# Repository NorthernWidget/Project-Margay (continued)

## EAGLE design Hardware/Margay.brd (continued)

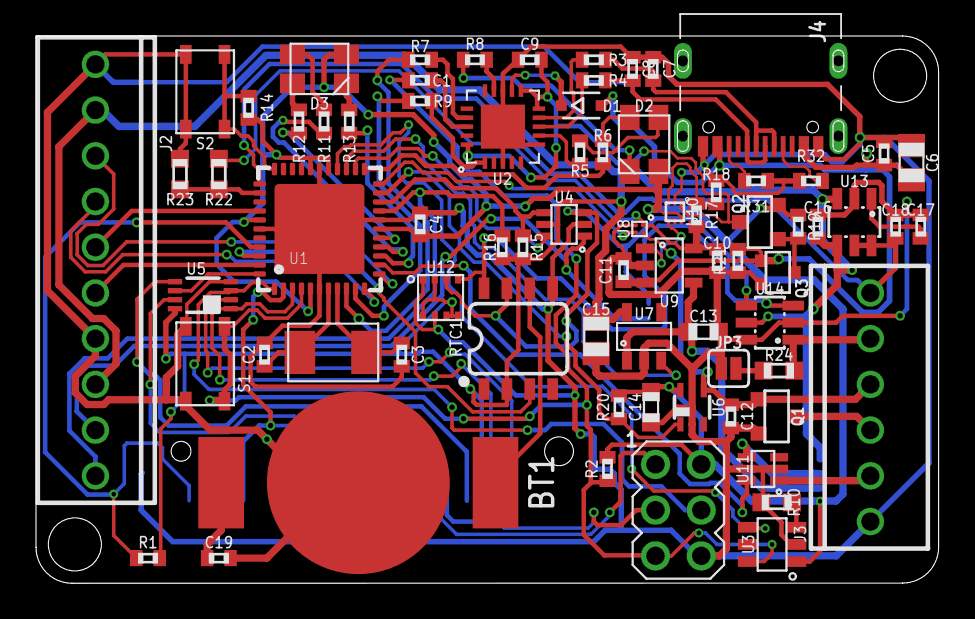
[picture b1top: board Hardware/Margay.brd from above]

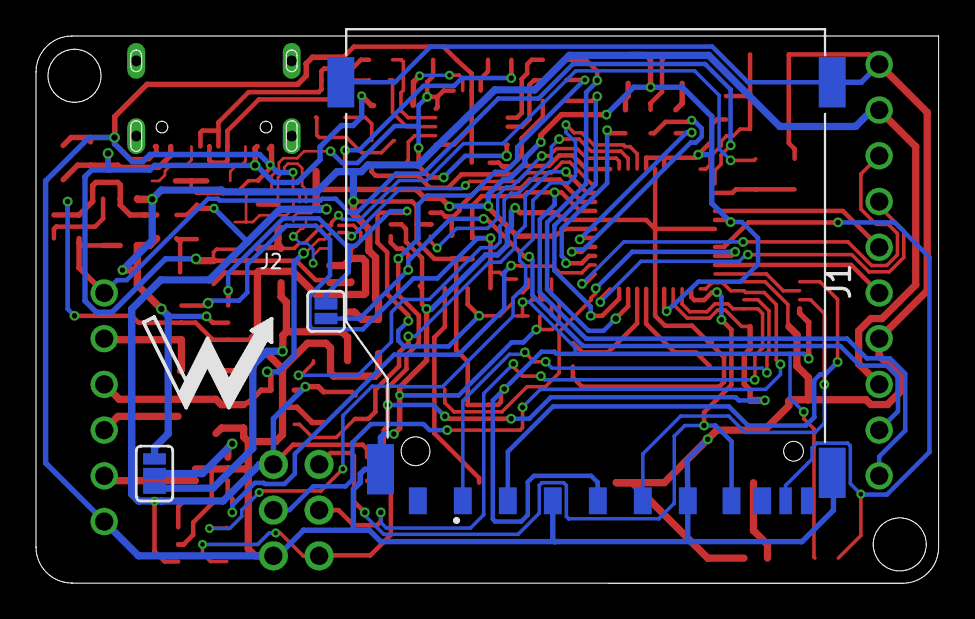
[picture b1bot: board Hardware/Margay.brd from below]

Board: 2 copper layers, 50.1 x 30.4 mm, 82 parts (4 on the bottom side), 72 nets.

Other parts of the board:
U$2: NWLOGO_MED

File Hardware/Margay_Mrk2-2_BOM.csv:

"Qty","Value","Device","Package","Parts","Description","DIGIKEY","DISP","MF","MOUSER","MPN","PROD_ID","VALUE","VALUE_PART",
"1","","CONN_102.54_SCREW","1X10_SCREW","J2","Genaric 10 terminal header","ED10567-ND","","On Shore","","OSTVN10A150","","","",
"11","0.1uF","C-EU0.1UFC0402","C0402","C1, C4, C5, C9, C10, C11, C12, C16, C17, C18, C19","CAPACITOR, European symbol","490-4759-1-ND","","Murata","","GCM155R71C104KA55D","","","",
"2","100k","R-EU_100KR0402","R0402","R10, R19","RESISTOR, European symbol","311-100KLRCT-ND","","Yageo","","RC0402FR-07100KL","","","100k",
"9","10k","R-EU_10KR0402","R0402","R1, R2, R14, R15, R16, R17, R18, R20, R21","RESISTOR, European symbol","311-10.0KLRCT-ND","","Yageo","","RC0402FR-0710KL","","","10k",
"2","10k","R-EU_10KR0603","R0603","R22, R23","RESISTOR, European symbol","311-10.0KHRCT-ND","","Yageo","","RC0603FR-0710KL","","","10k",
"1","10k","R-EU_P10KR0603","R0603","R24","RESISTOR, European symbol","P10KDBCT-ND","","Panasonic","","ERA-3AEB103V","","","10k",
"2","10uF","C-EU10UFC0805","C0805","C6, C15","CAPACITOR, European symbol","490-6473-6-ND","","Murata","","GRM21BR61C106KE15K","","","",
"4","12pF","C-EU12PFC0402","C0402","C2, C3, C7, C8","CAPACITOR, European symbol","445-5585-1-ND","","TDK","","CGA2B2C0G1H120J050BA","","","",
"2","1k","R-EU_1KR0402","R0402","R7, R9","RESISTOR, European symbol","311-1.00KLRCT-ND","","Yageo","","RC0603FR-07330RL","","","1k",
"2","1uF","C-EU1UFC0603","C0603","C13, C14","CAPACITOR, European symbol","587-1251-1-ND","","Yaiyo Yuden","","EMK107BJ105KA-T","","","",
"2","27","R-EU_27R0402","R0402","R3, R4","RESISTOR, European symbol","YAG3086CT-ND","","Yageo","","RC0402FR-0727RL","","","27",
"1","2N7002","MOSFET-NCH-2N7002PW","SOT323","Q3","N-channel MOSFETs","2N7002W-FDICT-ND","","Diodes Incorporated","","2N7002W-7-F","TRANS-11151","2N7002","",
"6","330","R-EU_330R0402","R0402","R5, R6, R8, R11, R12, R13","RESISTOR, European symbol","311-330LRCT-ND","","Yageo","","RC0402FR-07330RL","","","330",
"1","ATMEGA1284M","ATMEGA1284M","MLF44-TH","U1","8-bit Microcontroller with 128K Bytes In-System Programmable Flash","ATMEGA1284P-MURCT-ND","","Atmel","","ATMEGA1284P-MUR","","","",
"1","AVRISP-6","AVRISP-6","AVRISP","ISP1","AVR ISP HEADER","609-3234-ND","","Amphenol","","67997-206HLF","","","",
"1","BAT43WS","DIODESOD-323","SOD323-R","D1","Genaric Diode","BAT43WS-FDICT-ND","","Diodes Incorporated","","BAT43WS-7-F","","","",
"1","BATTERY_COIN12MM","BATTERY_COIN12MM","LINX_BAT-HLD-012-SMT","BT1","Coin Cell Battery Holder","BAT-HLD-012-SMT-ND","","Linx","","BAT-HLD-012-SMT","","","",
"1","BME280","BME280","BME280","U12","BME280 - Combined Digital Humidity and Pressure Sensor","828-1063-1-ND","BME280","Bosch","","BME280","","","",
"2","BUTTON4.2X3.2","BUTTON4.2X3.2","SWITCH_4.2X3.2","S1, S2","Genaric SPST Pushbutton","CKN10504CT-ND","","C&K","","PTS810 SJG 250 SMTR LFS","","","",
"2","CLVBA-FKA","CLVBA-FKA","CLVBA-FKA","D2, D3","Cree RGB LED, Small Package, Common Anode, CLVBA-FKA","CLVBA-FKA-CAEDH8BBB7A363CT-ND","","Cree","","CLVBA-FKA-CAEDH8BBB7A363","","","",
"1","CONN_6SCREW_2.54","CONN_6SCREW_2.54","1X06_SCREW","J3","Genaric 6 terminal header","ED10565-ND","","OnShore","","OSTVN06A150","","","",
"1","CRYSTAL8MHZ5X3.2","CRYSTAL8MHZ5X3.2","CRYSTAL_5X3.2_2-SMD","XTAL1","Crystal Oscilator","887-1740-1-ND","","TXC","","7A-8.000MAAE-T","","","",
"1","DMG3404","MOSFET-NCH-DMG3404L","SOT23-3","Q1","N-channel MOSFETs","DMG3404L-7DICT-ND","","Diodes Incorporated","","DMG3404L-7","","DMG3404","",
"1","DS3231M","DS3231M","SO08","RTC1","DS3231M Real Time Clock","DS3231MZ+-ND","","Maxim","","DS3231MZ+","","","",
"1","FDN360P","MOSFET_PCH-FDN360P","SOT23-3","Q2","P-channel MOSFETs","FDN360PCT-ND","","Fairchild","","FDN360P","","FDN360P","",
"1","FT231X-Q","FT231X-Q","QFN20","U2","FT231x - USB to UART Bridge","768-1128-1-ND","","FTDI","","FT231XQ-R","","","",
"1","JUMPER-SMT_2_NC_PASTE_SILK","JUMPER-SMT_2_NC_PASTE_SILK","SMT-JUMPER_2_NC_PASTE_SILK","JP3","Normally closed solder jumper","","","","","","","","",
"1","JUMPER-SMT_2_NO_SILK","JUMPER-SMT_2_NO_SILK","SMT-JUMPER_2_NO_SILK","JP1","Normally open jumper","","","","","","","","",
"1","JUMPER-SMT_3_1-NC_PASTE_SILK","JUMPER-SMT_3_1-NC_PASTE_SILK","SMT-JUMPER_3_1-NC_PASTE_SILK","JP2","Normally closed solder jumper (1 of 2 connections)","","","","","","","","",
"1","MAX6070AAUT18","MAX6070AAUT18","SOT23-6L","U13","MAX6070 Low Noise high precision voltage referance","MAX6070BAUT18+TCT-ND","","Maxim","","MAX6070BAUT18+T","","","",
"1","MCP3421A1","MCP3421A1","SOT23-6L","U14","MCP342* - Sigma Delta ADC","MCP3421A1T-E/CHCT-ND","MCP3421","Microchip","","MCP3421A1T-E/CH","","","",
"1","MIC94090C6","MIC94090C6","SC-70_6","U11","MIC9409x - Hight Side Load Switch","576-3484-1-ND","MIC94090","Microchip","","MIC94090YC6-TR","","","",
"1","MICRO_USB_LONGPADS","MICRO_USB_LONGPADS","10118194-0001LF_10118194-0001LF_LONGER_PADS","USB1","","609-4618-1-ND","","Amphenol","","10118194-0001LF","","","",
"1","SDMMC06132","SDMMC06132","06132","J1","SD MMC Card holder","A101492CT-ND","","TE","","2041021-4","","","",
"1","SN74AUP3G34DCU","SN74AUP3G34DCU","DCU_(R-PDSO-G8)","U5","SN74AUP3G34 - Logic Buffer","296-25595-1-ND","","TI","","SN74AUP3G34DCUR","","","",
"1","SN74LVC1G3157DRL","SN74LVC1G3157DRL","DRL_R-PDSO-N6","U4","SN74LVC1G3157 - SPDT Analog Switch","296-18015-1-ND","SN74LVC1G3157","TI","","SN74LVC1G3157DRLR","","","",
"1","TLV3691DPF","TLV3691DPF","DPF0006A","U10","TLV3691 - Nanopower Analog Comparator","296-37242-6-ND","","TI","","TLV3691IDPFR","","","",
"1","TPL5010DDC","TPL5010DDC","DDC_R-PDSO-G6","U3","TPL5010 - Nano-Power System Timer with Watchdog Functionality","296-38829-1-ND","","TI","","TPL5010DDCT","","","",
"1","TPS2104","TPS2104","SOT23-5","U9","TPS210x - Power Distribution Switch (OR'ing switch)","296-10882-1-ND","TPS2104","TI","","TPS2104DBVR","","","",
"1","TPS22916YFP","TPS22916YFP","YFP0004","U8","TPS22916 - Ultra Low Leakage Load Switch","296-47464-1-ND","","TI","","TPS22916CYFPT","","","",
"1","TPS79733","TPS79733","DCK_R-PDSO-G5","U6","TPS797* - Ultra Low Power Low Dropout Linear Regulator","296-11990-1-ND","TPS79733","TI","","TPS79733DCKR","","","",
"1","TPS7A0533DBV","TPS7A0533DBV","SOT23-5","U7","TPS7A05* - Ultra Low Power Low Dropout Linear Regulator","296-50256-1-ND","","TI","595-TPS7A0533PDBVR","TPS7A0533PDBVR","","","",

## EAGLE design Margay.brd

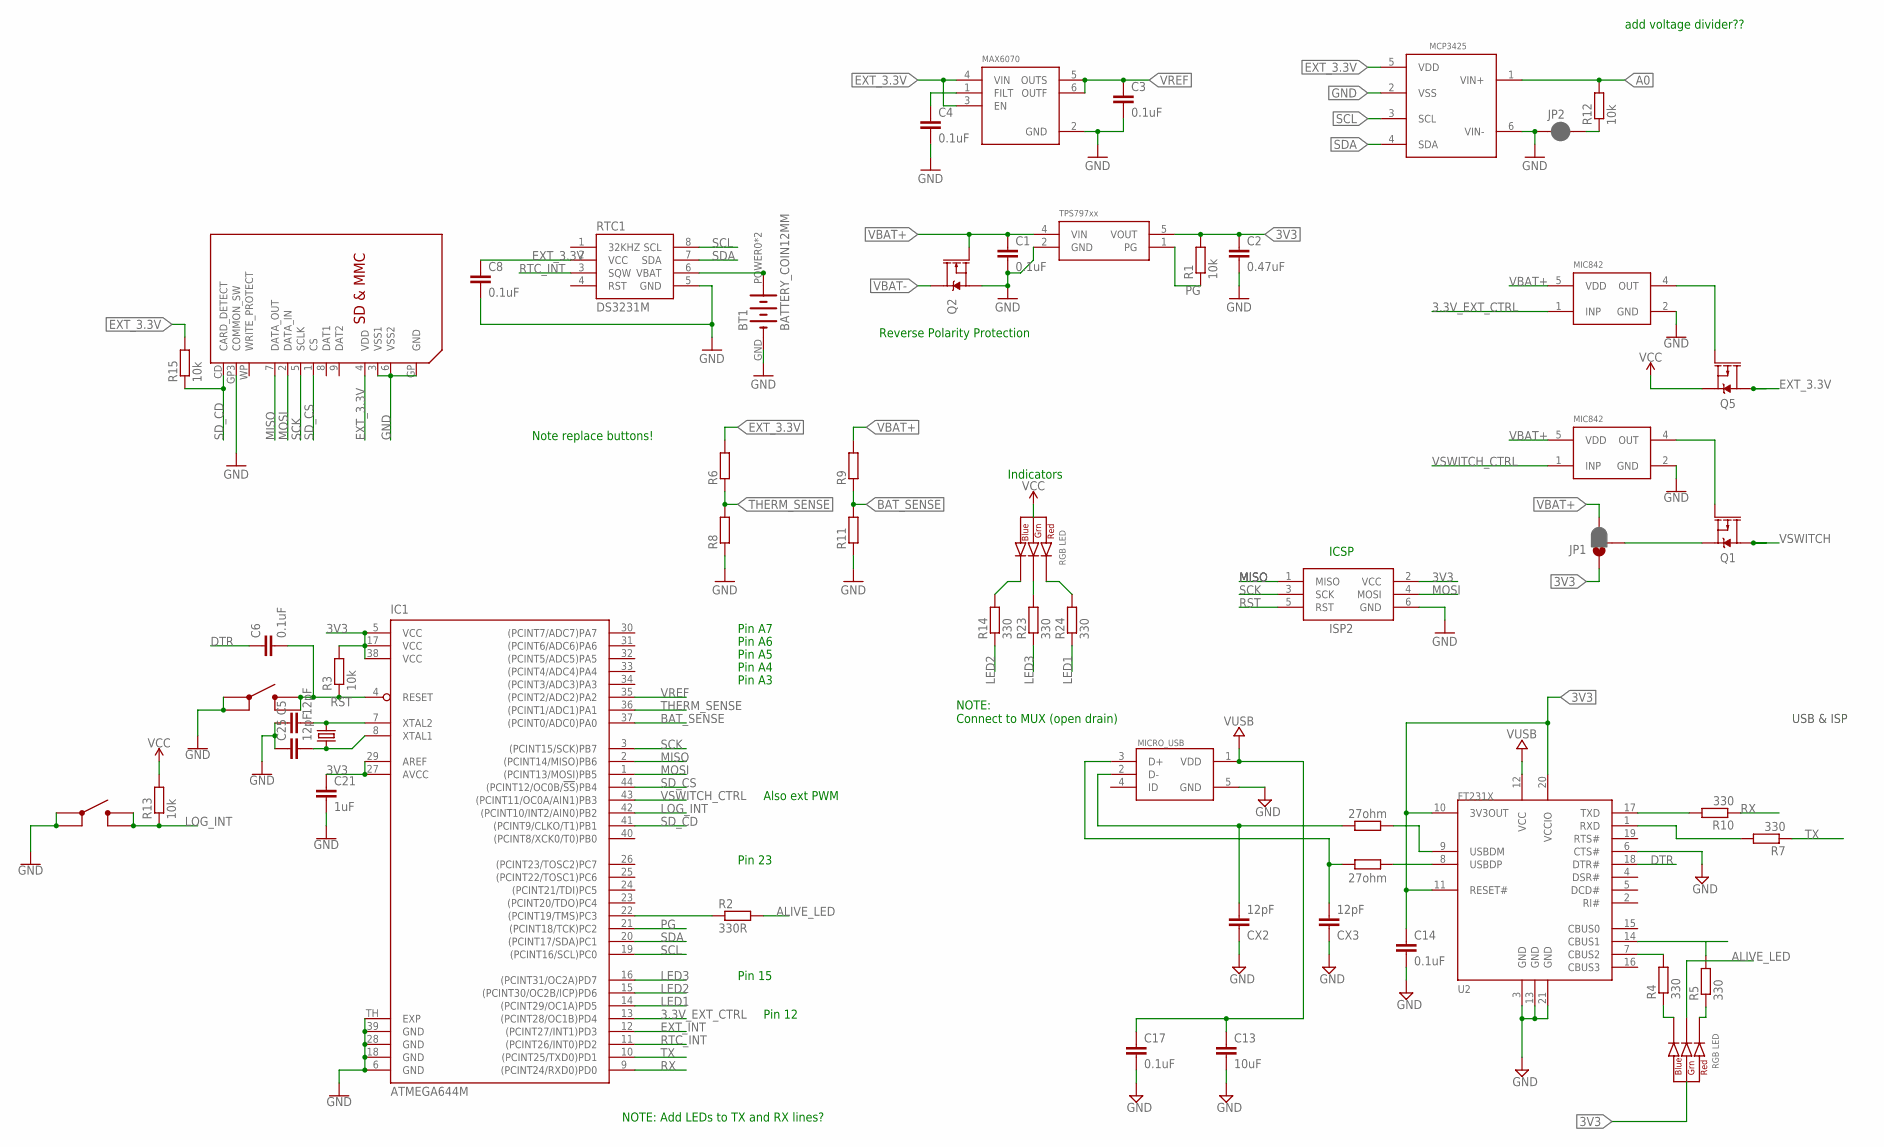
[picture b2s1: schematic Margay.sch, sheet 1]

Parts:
BT1: BATTERY_COIN12MM; AWICKERT_LINX_BAT-HLD-012-SMT
C1, C3, C4, C6, C8, C14, C17: 0.1uF; C0603
C2: 0.47uF; C0603
C5, C25: 12pF; C0603; MPN CL10C120JB8NNNC; DIGIKEY 1276-1254-1-ND
C13: 10uF; C0805
C21: 1uF; C0603; MPN CL10B105MO8NNWC; DIGIKEY 1276-6524-1-ND
CX2, CX3: 12pF; C0603
D+: 27ohm; R0603
D-: 27ohm; R0603
IC1: ATMEGA644M; MLF44-TH
ISP2: AVRISP-6; AVRISP; MPN 67997-206HLF; DIGIKEY 609-3234-ND
JP1: JUMPER-SMT_3_1-NC_PASTE_SILK; SMT-JUMPER_3_1-NC_PASTE_SILK
JP2: JUMPER-SMT_2_NC_PASTE_SILK; SMT-JUMPER_2_NC_PASTE_SILK
MICRO_USB: MICRO_USB_LONGPADS; 10118194-0001LF_10118194-0001LF_LONGER_PADS
Q1, Q5: MOSFET_PCH-IRLML2244; SOT23-3
Q2: MOSFET-NCH-DMG3404L; SOT23-3
R1, R12, R15: 10k; R0603
R2: 330R; R0603
R3, R13: 10k; R0603; DIGIKEY 311-10.0KHRCT-ND
R4, R7, R10, R14, R23, R24: 330; R0603; MPN RC0603FR-07330RL
R5: 330; R0603; MPN RC0603FR-07330RL; DIGIKEY 311-330HRCT-ND
R6, R8, R9, R11: R-EU_R0603; R0603
RTC1: DS3231M; SO08
U2: FT231X-Q; QFN20
U$1: CRYSTAL_5X3.2_2LEAD; CRYSTAL_5X3.2_2-SMD
U$3: SDMMC06132; 06132
U$4, U$18: MIC842; DCK_R-PDSO-G5
U$5, U$9: BUTTON4.2X3.2; SWITCH_4.2X3.2
U$6: TPS79733; DCK_R-PDSO-G5
U$7: MAX6070AAUT18; SOT23-6L
U$8: MCP3425; SOT23-6L
U$15, U$16: CLVBA-FKA

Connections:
3.3V_EXT_CTRL: IC1.13 ((PCINT28/OC1B)PD4), U$18.1 (INP)
3V3: C2.1, C14.1, C21.1, IC1.5 (VCC), IC1.17 (VCC), IC1.27 (AVCC), IC1.29 (AREF), IC1.38 (VCC), ISP2.2 (VCC), JP1.1, Q5.2 (S), R1.2, R3.2, R13.2, U2.10 (3V3OUT), U2.11 (RESET#), U2.20 (VCCIO), U$6.5 (VOUT), U$15.2 (ANODE), U$16.2 (ANODE)
A0: R12.2, U$8.1 (VIN+); also elsewhere on the board
ALIVE_LED: R2.2, U$16.4 (GREEN_CATH)
BAT_SENSE: IC1.37 ((PCINT0/ADC0)PA0), R9.1, R11.2
DTR: C6.1, U2.18 (DTR#)
EXT_3.3V: C8.1, Q5.3 (D), R6.2, R15.2, RTC1.2 (VCC), U$3.4 (VDD), U$7.3 (EN), U$7.4 (VIN), U$8.5 (VDD); also elsewhere on the board
EXT_INT: IC1.12 ((PCINT27/INT1)PD3); also elsewhere on the board
GND: BT1.GND (-), C1.2, C2.2, C3.2, C4.2, C5.1, C8.2, C13.2, C14.2, C17.2, C21.2, C25.1, CX2.1, CX3.1, IC1.6 (GND), IC1.18 (GND), IC1.28 (GND), IC1.39 (GND), IC1.TH (EXP), ISP2.6 (GND), JP2.1, MICRO_USB.5 (GND), Q2.2 (S), R8.1, R11.1, RTC1.5 (GND), U2.3 (GND), U2.6 (CTS#), U2.13 (GND), U2.21 (GND), U$3.3 (VSS1), U$3.6 (VSS2), U$3.GP (GND), U$3.GP3 (COMMON_SW), U$4.2 (GND), U$5.1, U$5.2, U$6.2 (GND), U$7.2 (GND), U$8.2 (VSS), U$8.6 (VIN-), U$9.1, U$9.2, U$18.2 (GND); also elsewhere on the board
LED1: IC1.14 ((PCINT29/OC1A)PD5), R24.1
LED2: IC1.15 ((PCINT30/OC2B/ICP)PD6), R14.1
LED3: IC1.16 ((PCINT31/OC2A)PD7), R23.1
LOG_INT: IC1.42 ((PCINT10/INT2/AIN0)PB2), R13.1, U$5.3 (4), U$5.4 (3)
MISO: IC1.2 ((PCINT14/MISO)PB6), ISP2.1 (MISO), U$3.7 (DATA_OUT); also elsewhere on the board
MOSI: IC1.1 ((PCINT13/MOSI)PB5), ISP2.4 (MOSI), U$3.2 (DATA_IN); also elsewhere on the board
unnamed: IC1.22 ((PCINT19/TMS)PC3), R2.1
unnamed: Q1.1 (G), U$4.4 (OUT)
unnamed: JP1.2, Q1.2 (S)
unnamed: C5.2, IC1.7 (XTAL2), U$1.OSC2 (2)
unnamed: Q5.1 (G), U$18.4 (OUT)
unnamed: C25.2, IC1.8 (XTAL1), U$1.OSC1 (1)
unnamed: R14.2, U$15.3 (BLUE_CATH)
unnamed: R23.2, U$15.4 (GREEN_CATH)
unnamed: C4.1, U$7.1 (FILT)
unnamed: JP2.2, R12.1
unnamed: R24.2, U$15.1 (RED_CATH)
unnamed: R5.1, U$16.1 (RED_CATH)
unnamed: R10.2, U2.17 (TXD)
unnamed: R4.1, U$16.3 (BLUE_CATH)
unnamed: BT1.POWER0 (+), BT1.POWER1 (+), RTC1.6 (VBAT)
unnamed: R7.2, U2.1 (RXD)
unnamed: CX3.2, D+.2, MICRO_USB.3 (D+)
unnamed: CX2.2, D-.2, MICRO_USB.2 (D-)
unnamed: D+.1, U2.8 (USBDP)
unnamed: R4.2, U2.7 (CBUS2)
unnamed: R5.2, U2.14 (CBUS1)
unnamed: D-.1, U2.9 (USBDM)
PG: IC1.21 ((PCINT18/TCK)PC2), R1.1, U$6.1 (PG)
RST: C6.2, IC1.4 (RESET), ISP2.5 (RST), R3.1, U$9.3 (4), U$9.4 (3)
RTC_INT: IC1.11 ((PCINT26/INT0)PD2), RTC1.3 (SQW)
RX: IC1.9 ((PCINT24/RXD0)PD0), R10.1
SCK: IC1.3 ((PCINT15/SCK)PB7), ISP2.3 (SCK), U$3.5 (SCLK); also elsewhere on the board
SCL: IC1.19 ((PCINT16/SCL)PC0), RTC1.8 (SCL), U$8.3 (SCL); also elsewhere on the board
SDA: IC1.20 ((PCINT17/SDA)PC1), RTC1.7 (SDA), U$8.4 (SDA); also elsewhere on the board
SD_CD: IC1.41 ((PCINT9/CLKO/T1)PB1), R15.1, U$3.CD (CARD_DETECT)
SD_CS: IC1.44 ((PCINT12/OC0B/!SS!)PB4), U$3.1 (CS)
THERM_SENSE: IC1.36 ((PCINT1/ADC1)PA1), R6.1, R8.2
TX: IC1.10 ((PCINT25/TXD0)PD1), R7.1
VBAT+: C1.1, JP1.3, Q2.1 (G), R9.2, U$4.5 (VDD), U$6.4 (VIN), U$18.5 (VDD); also elsewhere on the board
VBAT-: Q2.3 (D); also elsewhere on the board
VREF: C3.1, IC1.35 ((PCINT2/ADC2)PA2), U$7.5 (OUTS), U$7.6 (OUTF); also elsewhere on the board
VSWITCH: Q1.3 (D); also elsewhere on the board
VSWITCH_CTRL: IC1.43 ((PCINT11/OC0A/AIN1)PB3), U$4.1 (INP)
VUSB: C13.1, C17.1, MICRO_USB.1 (VDD), U2.12 (VCC)

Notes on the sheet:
Indicators
NOTE: Connect to MUX (open drain)
Note replace buttons!
Pin 12
Pin A7
Pin A6
Pin A5
Pin A4
Pin 15
NOTE: Add LEDs to TX and RX lines?
USB & ISP
Pin 23
Pin A3
Also ext PWM
ICSP
add voltage divider??
Reverse Polarity Protection

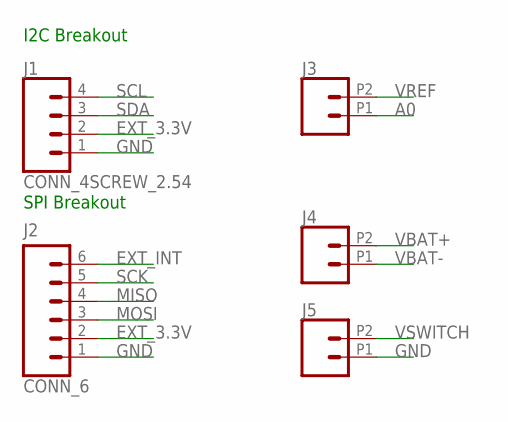
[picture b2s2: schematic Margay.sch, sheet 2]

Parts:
J1: CONN_4SCREW_2.54; 1X04
J2: CONN_6; 1X06_SCREW
J3, J4, J5: CONN_022.54MM_SCREWTERM; 1X02_2.54_SCREWTERM

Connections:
A0: J3.P1 (1); also elsewhere on the board
EXT_3.3V: J1.2, J2.2; also elsewhere on the board
EXT_INT: J2.6; also elsewhere on the board
GND: J1.1, J2.1, J5.P1 (1); also elsewhere on the board
MISO: J2.4; also elsewhere on the board
MOSI: J2.3; also elsewhere on the board
SCK: J2.5; also elsewhere on the board
SCL: J1.4; also elsewhere on the board
SDA: J1.3; also elsewhere on the board
VBAT+: J4.P2 (2); also elsewhere on the board
VBAT-: J4.P1 (1); also elsewhere on the board
VREF: J3.P2 (2); also elsewhere on the board
VSWITCH: J5.P2 (2); also elsewhere on the board

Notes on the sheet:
I2C Breakout
SPI Breakout

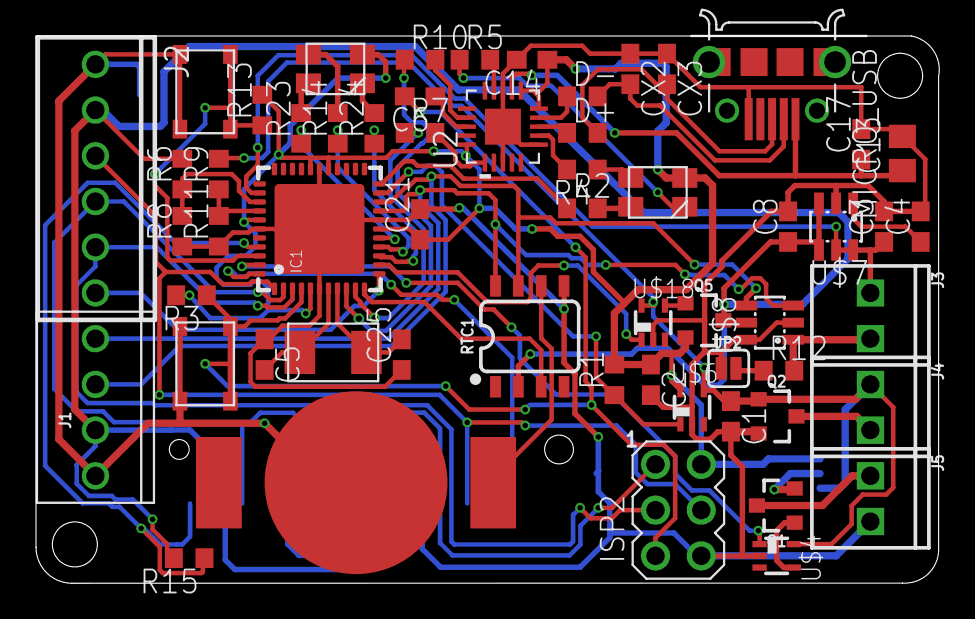
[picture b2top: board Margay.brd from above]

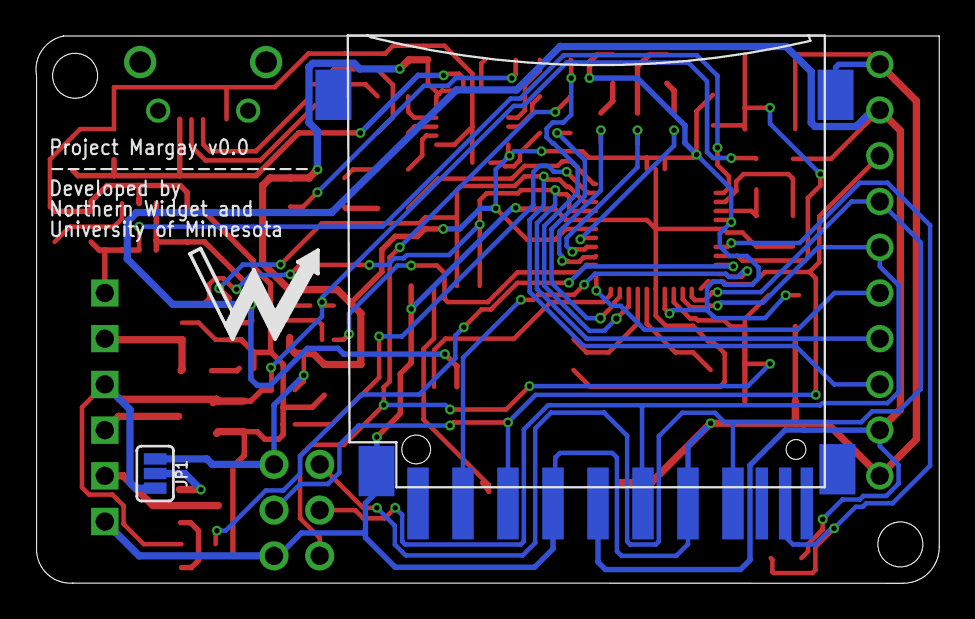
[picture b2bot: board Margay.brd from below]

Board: 2 copper layers, 50.2 x 30.4 mm, 61 parts (3 on the bottom side), 54 nets.

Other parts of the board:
U$2: NWLOGO_MED

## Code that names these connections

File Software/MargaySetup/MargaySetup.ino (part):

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const uint8_t ThermSense_Pin = 1;
const uint8_t BatSense_Pin = 2;

const uint8_t VSwitch_Pin = 12;
const uint8_t SD_CD = 1;

const uint8_t Ext3v3Ctrl = 19;
const uint8_t ExtInt = 11;
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
const uint8_t RGB[] = {RED, GREEN, BLUE};

const int SD_CS = 4;
char FileNameC[11];
boolean SD_Init = false;

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}

void IOTest() {
  pinMode(VSwitch_Pin, OUTPUT);
  pinMode(ExtInt, OUTPUT);

  while(Serial.read() != '\r') {
    digitalWrite(VSwitch_Pin, LOW);
    digitalWrite(ExtInt, LOW);
    delay(1000);
    digitalWrite(VSwitch_Pin, HIGH);
    digitalWrite(ExtInt, HIGH);
    delay(1000);
  }
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
boolean TestSD() {
  boolean SDError = false;
  pinMode(SD_CS, OUTPUT);
  SPI.setDataMode(SPI_MODE0);
  SPI.setClockDivider(SPI_CLOCK_DIV2);

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
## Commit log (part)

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2018-03-01 First commit, schematic complete, board routing in progress
2018-03-01 Preliminary layout done, fixed led issue
    Finished with first round layout, changed supply voltage for LEDs to be 3v3 instead of VUSB so that alive led can work regardless of use of USB voltage
2018-03-02 Edits for 0.1"compatability
2018-03-03 Minor edits, generated gerbers
2018-03-06 Final Gerbers, renamed design
2018-04-04 updated readme again
    Added software description to readme, software to be promptly added!
2018-04-04 Added software folder to repo
    Software folder containing hardware test script as well as logger code which supports the TP-Downhole
2018-04-04 Updated readme
    Updated DS3231_Logger link in readme, now that this repo actually exists
2018-04-09 Minor moddifications to software
2018-04-09 Added revision notes to board
2018-04-11 Margay 1.0 initial layout
    Initial layout of the version 1.0 , solder jumpers currently not added, along with battery connector, may intoduce back later, needs cleanup and DRC
2018-04-12 Cleaned up board, removed power switch
    Cleaned up the routing, removed the switched power
2018-04-12 Updated board, fixed software logging time
    Cleaned up traces on board, changed battery in schematic, updated logging program to have 15 minute interval by default
2018-04-16 Generated gerbers, ready for Mrk1
2018-04-16 Fixed silk screen in gerbers
2018-05-03 Added stencil files and updated/fixed logger code
    Added solder stencil files and fixed the temp conversion issue in the logger code, and added a blink to indicate when the log button is pressed
2018-05-03 Edits to software for default time and baro mode
    Added dedicated baro sketch file, and changed default saved logging time to be 15 minutes s
2018-06-01 Minor mod to hardware test, added BOM
    Added independent BOM and did some clean up on the schematic
2018-06-01 Added frames, major schematic clean up
    Added frames and cleaned up and divided schematic into additional sheets
2018-06-06 Updated board to account for part changes
    Fixed issue where 2x1 connectors displaced, also updated passives to new sizes
2018-06-06 Updated passive size
2018-06-06 Changed folder arraignment
2018-06-13 semicolons to commas in CSV
2018-06-28 Updated test files, pick and place info, and fixed part info
2018-06-28 Updated licence
2018-07-12 Added reference designators and legacy hardware test
    Added legacy hardware testing file and reference designator image
2018-09-07 Software power fix in hardware test, added dedicated v0 and v1 test scripts
    Changed power sequencing in the hardware test script, added a dedicated v0 and v1 version for the Margay test file
2018-09-07 Fixed button layout (#14)
    Updated button layout from Cold Silicon updates, fixed resulting layout issues
2018-09-10 Cleaned up schematic, added board and schematic images for v1.0
    Added documentation for version 1.0, added schematic PDF, board images, and updated BOM to fix ADC part number
2018-09-10 First round of v2 updates to schematic
2018-09-14 Revised schematic for Margay v2, added circuit simulations
    Will remove some simulations later, still need to do much layout and placement, as well as verify the schematic
2018-09-14 Updated simulation names, gitignore, clean
    Cleaned out bulk files, changed simulation names, added LTSpice files to gitignore
2018-09-15 Begining of v2 layout
    Power section and severl problematic signals taken care of, still need to add BME280 and fix header connections
2018-09-17 Main v2 layout complete, needs review minor cleanup
    Main layout is completed, needs verification and review for any traces which need to be cleaned up. Double check power on schematic!
2018-09-18 Cleanup and silkscreen
    Cleanup of traces, minor fix to overlap problem, relabeled silk screen to match new connections
2018-09-26 1Mb file size
2018-09-26 Added pin description section to README
    Added list of pins and a brief description of their features to the readme
2018-10-02 Added developer notes to readme
2018-10-02 Fixed symbols in readme
    Forgot `&` in HTML symbol formatting in readme to OMEGA did not format properly
2018-10-31 Updated model info in readme
2018-10-31 Added note about 3.3v logic in readme
2019-01-05 Condensed headers, added bat cap, added WDT
    Condensed headers into 2 single piece headers, added capacitor on backup battery to deal with debouncing issue, also added WDT unit and replaced switched voltage output driver with unit switch instea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
2019-01-07 xtal cap GND tweak, E hdr flush
2019-01-07 label RTC_BAT+
2019-01-07 Updated to new battery
    Updated battery part to fix airwire issue
2019-03-20 In progress of power switch upgrade
    Midway through upgrade of power switch topology
2019-03-20 improvements to aux power switch, layout complete
    Completed layout of new aux power switch topology
2019-03-21 Updated paste patterns, generated paste gerbers
    Generated solder paste gerbers and updated paste layout to be more correct (~60% on body pads)
2019-03-21 Added v2 Gerbers
2019-04-03 Updates for v2.1
    Added in schematic and board updates for v2.1, voltage divider on input to comparator, and diode in series with FTDI
2019-04-13 v2.1, sent to fab
    Minor board cleanup and generated gerbers for fab
2019-04-21 CC BY-SA 4.0 International: official wording
2019-04-30 Added part numbers, moved part identifiers
2019-05-07 Changed auto power switch topology, cleanup desired
    Changed auto power switch to use active low logic
2019-05-12 Minor cleanup, generated gerbers, sent v2.2 to fab
2019-07-19 Minor edits and cleanup for manufacture submission
2019-07-31 2-page guide
2019-08-06 Added reference ID docs
2019-08-15 Cleaned up schematic and updated BoM for v2.2
2019-09-12 Updated BoM, corelated with schematic
    Fixed SD card issue, fixed 0603 vs 0402 issue
2020-04-26 rm outdated diagrams
2020-04-26 Pick and Place files a good idea, but these are outdated
2020-04-26 Outdated stencil files
2020-04-26 Duplicate of Margay.csv
2020-04-26 Presuming this renumbering is done, this file can live on in archives
2020-04-26 Fabrication layout diagrams to their own folder
2020-04-26 Earlier version
2020-04-26 v1 Gerbers
2020-04-26 rm 2.x Gerbers older than current revision
2020-04-26 Only one Gerber zip; no need for folder unless we break these out again
2020-04-26 rm v0 and v1 tests, etc.
2020-04-30 Battery and Margay box mounts; fab stencil
2020-05-01 GNU GPL v3 for code products (software, firmware, etc.)
2020-05-03 Labeled all jumpers, including Vdiv schematic
2020-06-06 Schematic images
2020-06-06 Vector diagram for analog jumper on silk
2020-06-06 Vdiv jumper on board front
2020-06-18 Sources of support
2020-06-18 Remove blank line between images
2021-02-20 Example code and notes on updated guide.
2021-02-28 scrapped initial changes (not good enough), left comments for intent
2021-02-28 ODT and PDF to git LFS
2021-02-28 Opaque white background to see black text
2021-03-01 Default Vs=Vswitch connected to 3V3_AUX via solder paste on jumper
2021-03-01 Swap + fix SDA OB and SDA EXT jumper labels
2021-03-02 Removed erroneous top silk
2021-03-02 Vdiv diagram on back for jp on front
2021-03-02 Zenodo DOI badge
2021-03-02 Added v2.2 Gerbers
2021-03-07 First round of document organizing
2021-03-10 On-board I2C, SPI, and UART devices
2021-03-11 Minor rewording
2021-03-12 Reformatting operation guide pt. 1
2021-03-12 Typo fix/note for myself for the future
2021-03-15 Small consistency changes: reorganizing lists, bolding, etc.
2021-04-02 shuffling tech specs, small changes
2021-04-06 reorganized sections, couple of typos
2021-04-07 Use carriage return or newline/linefeed
2021-04-07 Setting the serial number
2021-04-13 Initial final version
2021-04-13 Mounting plate for WQ-48 box Untested as of yet; if no new commits in a few days, it works!
2021-04-14 Holes for #4 screws; reposition resistors and traces
2021-04-16 No 4 screw holes: tight fit (ColdSilicon lbr)
2021-04-16 Updated for both orientations and No.4 holes
2021-04-16 Route SW trace to open space for metal stand-off
2021-05-10 100K 0402 --> 0603 for easier replacement This is on the WDT-setting resistor (R10) I changed a second resistor (R19) associated with the power system to fully convert the 0402s to 0603s and keep the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
2021-07-05 update "Margay_NoSensors.ino"
    Remove unused variables
    Make "header" lowercase per code style standards
2021-07-05 Margay_NoSensors: Update/fix comments
2021-07-17 Update sample code for library updates
    Margay can be instantiated without passing arguments
    Run --> run
2021-07-17 v2.3 on back silk
2021-07-19 ISP driver note
2021-07-19 margay blue logging blink updated
2021-08-08 note consistency changes
2021-08-08 note consistency changes pt. 2
2022-04-26 Update wire names: match code and silk
2022-05-01 USB-C conversion in progress: moving parts
2022-05-01 USB C: Components placed; routing
2022-05-01 USB-C: Routing complete; DRC passed
2022-05-02 ~65:47 WDT 130K resistor 0603 1 hour logging intervals seem like a common desire. Our 100K resistor reset the logger after ~59:40, permitting a dangerous edge case (that Yuan Zeng found) by which the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
2022-05-09 Fixes to v2.3 update
    - VUSB and VBUS connected
    - Moved vias from underneath USB connector
    - Separated Analog GND region from USB GND region to reduce noise
    - Fixed 3v3 routing (current limiting path between input and MCU)
    - Moved the "Project Margay" label on bottom to try to have it less disrupted by the solder-mask stops
2022-05-09 Updated 5.1kΩ resistors
    Updated 5.1kΩ resistors to use bschulz_passives library item
2022-05-18 Max voltage
    Absolute max in comment; recommended shows up in rendered Markdown
2022-06-22 LONG short short good flash
2022-10-12 Bobby Schulz' ORCID
2022-10-13 Update UMN ESCI image
2023-01-22 Incorrect license CC-BY-SA 4.0 is (see LICENSE.md)
2023-03-17 Updated parts for production
    - XTAL
    - XTAL Caps
    - Jumpers (DNP)
    - TPS2104
    - MAX6070
2023-03-17 Updated SD card and analog switch
2023-03-17 Updated BoMs
2023-03-20 2v2 BoM alongside others
2023-04-13 Updated readme for v2.2 and VSwitch info
    Added pinout info for v2.2 logger and added current/power output limits for VSwitch
2023-07-27 Added mount file for v3.0
2023-10-25 Revise license text to proper Markdown version.
2024-11-02 Added documentation and production info
2025-12-11 Change MAX 6071 to 6070 on v3.0 BoM by hand
    Unintentional v2.3 to 3.0 change: the 6070 is what we need. We should check if the 6071 or the 6070 is included in the PCB definition, now or once we transition to KiCAD.
    We noted this error because of faulty (doubled) battery-voltage readings in the cold.
    From Bobby Schulz, who found the source of the error:
    This is important because the MAX6071 does not have an internal filter and as a result the pinout changes - see Page 19 of datasheet. This pinout changes pin 1 from the filtered input (how we intende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
2026-06-01 3V3 --> Schottky diode --> VCoin+. Provide a backup option for the clock if its battery fails: the main batteries of the data logger. Ideally, this would have been connected to VBat to keep the coin 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
2026-06-01 Autoformat from one line.
2026-06-01 Add extra 1 uA decoupling cap for DS3231M. The 0.1uF cap is right by the battery, which is fine. But there was not as much buffering of power changes right by the DS3231M. And the DS3231M responds be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
    Claude Code did a quick calculation based on my finding of an up to 300 us
    lag: this is the time required for a VBat handoff.
    C = I × t / ΔV = 0.3 mA × 300 µs / 0.25 V = 0.36 µF
    This extra capacitor might not be necessary, but considering the importance
    of the RTC and the fact that we have space, I am aiming these commits to
    ensure that the RTC is properly buffered from power changes and stays running.
2026-06-01 Unify 10K resistors to CRT0603-BY-1002ELFCT-ND.
2026-06-01 Oval slots for USB C mechanical feet.
2026-06-02 Update pad-size defaults based on oval holes for USB C feet.

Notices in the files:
parts and their libraries:
microbuilder: This work is placed in the public domain, and may be freely used for commercial and non-commercial work with the following conditions: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
SparkFun-PowerSymbols: Licensing: Creative Commons ShareAlike 4.0 International - https://creativecommons.org/licenses/by-sa/4.0
